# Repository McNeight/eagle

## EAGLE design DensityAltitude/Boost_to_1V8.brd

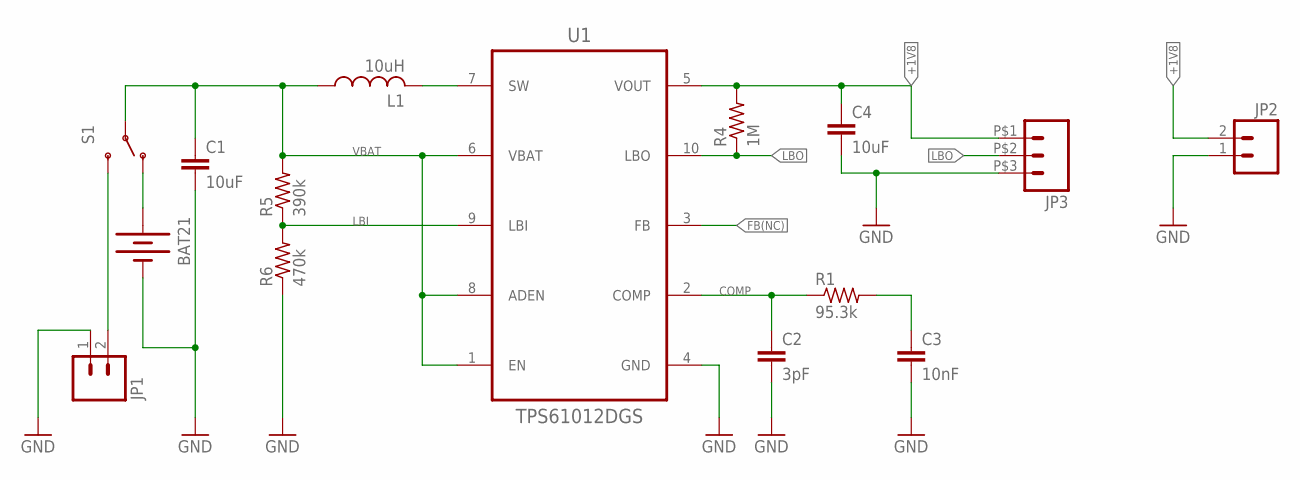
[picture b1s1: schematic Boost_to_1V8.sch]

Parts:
BAT21: BATTERYAA; BATTERY-AA
C1, C4: 10uF; C1812
C2: 3pF; C0805
C3: 10nF; C0805
JP1, JP2: M02JST-PTH-2; JST-2-PTH
JP3: M03; 1X03_282834-3
L1: 10uH; CDRH6D38
R1: 95.3k; R0805
R4: 1M; R0805
R5: 390k; R0805
R6: 470k; R0805
S1: SWITCH-SPDTPTH; SWITCH-SPDT
U1: TPS61012DGS; SOP50P490X110-10N

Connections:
+1V8: C4.1, JP2.2, JP3.P$1 (1), R4.2, U1.5 (VOUT)
BAT+: BAT21.PWR@1 (+), BAT21.PWR@2 (+), S1.1 (O)
COMP: C2.1, R1.1, U1.2 (COMP)
FB(NC): U1.3 (FB)
GND: BAT21.GND@1 (-), BAT21.GND@2 (-), C1.2, C2.2, C3.2, C4.2, JP1.1, JP2.1, JP3.P$3 (3), R6.1, U1.4 (GND)
LBI: R5.1, R6.2, U1.9 (LBI)
LBO: JP3.P$2 (2), R4.1, U1.10 (LBO)
unnamed: C3.1, R1.2
unnamed: JP1.2, S1.3 (S)
SW: L1.P$2 (2), U1.7 (SW)
VBAT: C1.1, L1.P$1 (1), R5.2, S1.2, U1.1 (EN), U1.6 (VBAT), U1.8 (ADEN)

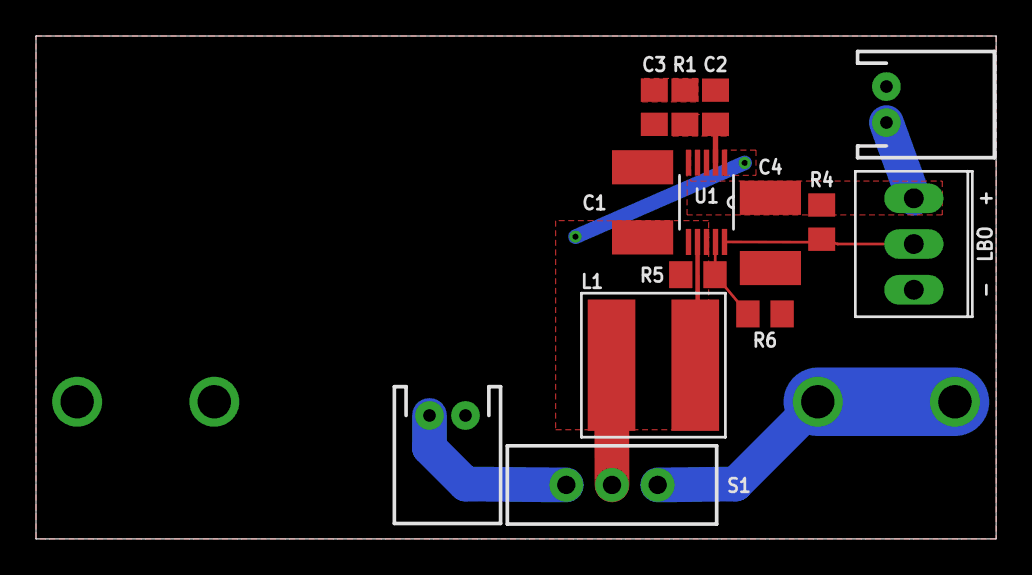
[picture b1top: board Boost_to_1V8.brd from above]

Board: 2 copper layers, 53.3 x 27.9 mm, 15 parts (1 on the bottom side), 10 nets.

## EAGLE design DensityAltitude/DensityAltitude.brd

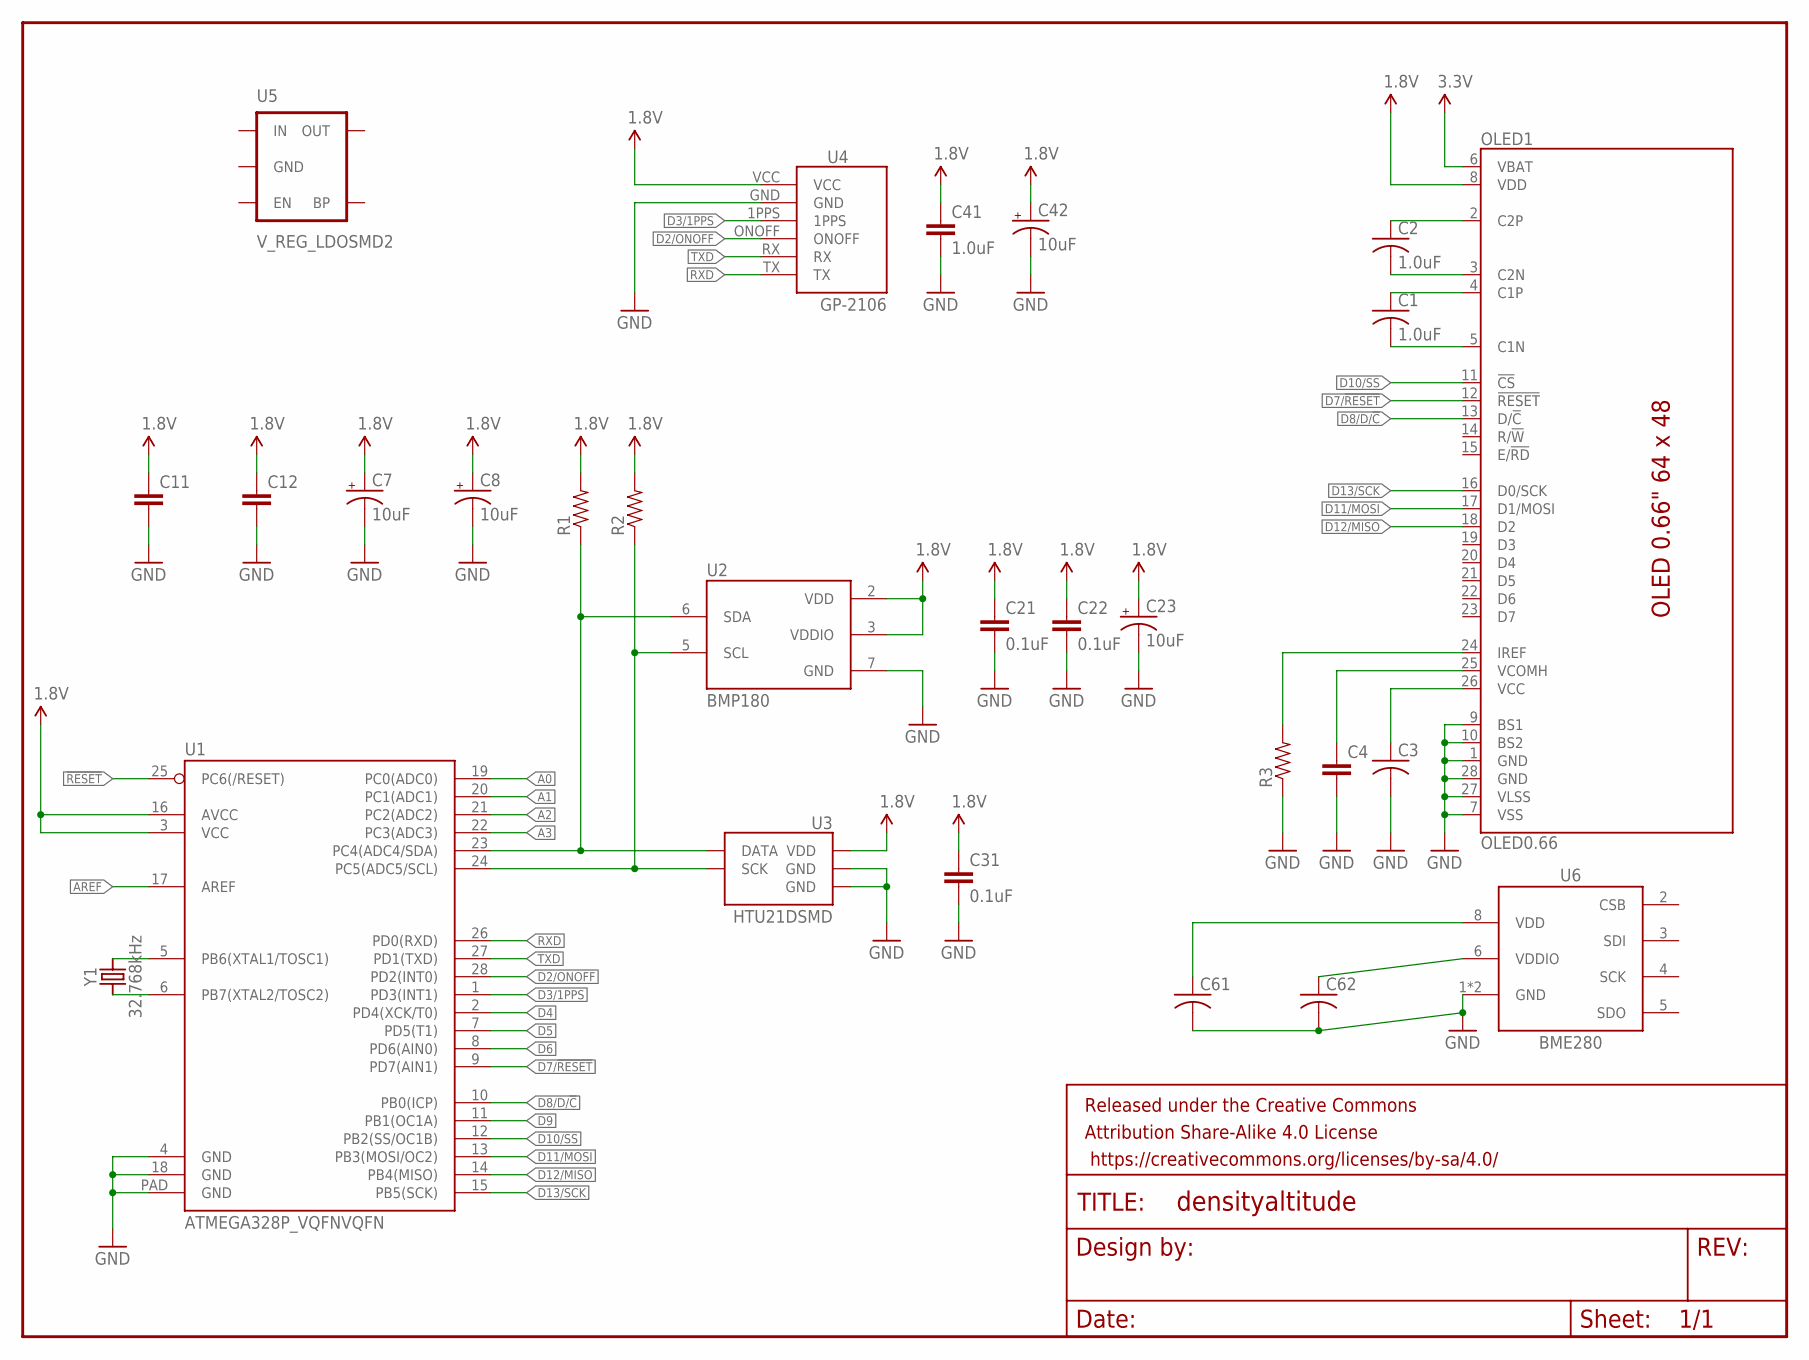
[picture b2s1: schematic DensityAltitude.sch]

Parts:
C1, C2: 1.0uF; C0201
C3, C61, C62: C-USC0201; C0201
C4, C11, C12: CAP0402-CAP; 0402-CAP
C7, C8, C23, C42: 10uF; EIA3216
C21, C22, C31: 0.1uF; 0402-CAP
C41: 1.0uF; 0402-CAP
FRAME1: FRAME-LETTER; CREATIVE_COMMONS
OLED1: OLED0.66; OLED-0.66-64X48
R1, R2, R3: RESISTOR0402-RES; 0402-RES
U1: ATMEGA328P_VQFNVQFN; VQFN-28
U2: BMP180
U3: HTU21DSMD; HTU21D
U4: GP-2106
U5: V_REG_LDOSMD2; SC70
U6: BME280
Y1: 32.768kHz; 2-SMD

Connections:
1.8V: C7.A (+), C8.A (+), C11.1, C12.1, C21.1, C22.1, C23.A (+), C31.1, C41.1, C42.A (+), OLED1.8 (VDD), R1.2, R2.2, U1.3 (VCC), U1.16 (AVCC), U2.2 (VDD), U2.3 (VDDIO), U3.VDD, U4.VCC
3.3V: OLED1.6 (VBAT)
!RESET: U1.25 (PC6(/RESET))
A0: U1.19 (PC0(ADC0))
A1: U1.20 (PC1(ADC1))
A2: U1.21 (PC2(ADC2))
A3: U1.22 (PC3(ADC3))
A4/SDA: R1.1, U1.23 (PC4(ADC4/SDA)), U2.6 (SDA), U3.DATA
A5/SCL: R2.1, U1.24 (PC5(ADC5/SCL)), U2.5 (SCL), U3.SCK
AREF: U1.17 (AREF)
D2/ONOFF: U1.28 (PD2(INT0)), U4.ONOFF
D3/1PPS: U1.1 (PD3(INT1)), U4.1PPS
D4: U1.2 (PD4(XCK/T0))
D5: U1.7 (PD5(T1))
D6: U1.8 (PD6(AIN0))
D7/!RESET: OLED1.12 (!RESET!), U1.9 (PD7(AIN1))
D8/D/!C: OLED1.13 (D/!C!), U1.10 (PB0(ICP))
D9: U1.11 (PB1(OC1A))
D10/SS: OLED1.11 (!CS!), U1.12 (PB2(SS/OC1B))
D11/MOSI: OLED1.17 (D1/MOSI), U1.13 (PB3(MOSI/OC2))
D12/MISO: OLED1.18 (D2), U1.14 (PB4(MISO))
D13/SCK: OLED1.16 (D0/SCK), U1.15 (PB5(SCK))
GND: C3.2, C4.2, C7.C (-), C8.C (-), C11.2, C12.2, C21.2, C22.2, C23.C (-), C31.2, C41.2, C42.C (-), C61.2, C62.2, OLED1.1 (GND), OLED1.7 (VSS), OLED1.9 (BS1), OLED1.10 (BS2), OLED1.27 (VLSS), OLED1.28 (GND), R3.1, U1.4 (GND), U1.18 (GND), U1.PAD (GND), U2.7 (GND), U3.7 (GND), U3.GND, U4.GND, U6.1 (GND), U6.7 (GND)
unnamed: C62.1, U6.6 (VDDIO)
unnamed: C61.1, U6.8 (VDD)
unnamed: U1.5 (PB6(XTAL1/TOSC1)), Y1.2
unnamed: U1.6 (PB7(XTAL2/TOSC2)), Y1.1
unnamed: C2.1, OLED1.2 (C2P)
unnamed: C2.2, OLED1.3 (C2N)
unnamed: C1.1, OLED1.4 (C1P)
unnamed: C1.2, OLED1.5 (C1N)
unnamed: C3.1, OLED1.26 (VCC)
unnamed: C4.1, OLED1.25 (VCOMH)
unnamed: OLED1.24 (IREF), R3.2
RXD: U1.26 (PD0(RXD)), U4.TX
TXD: U1.27 (PD1(TXD)), U4.RX

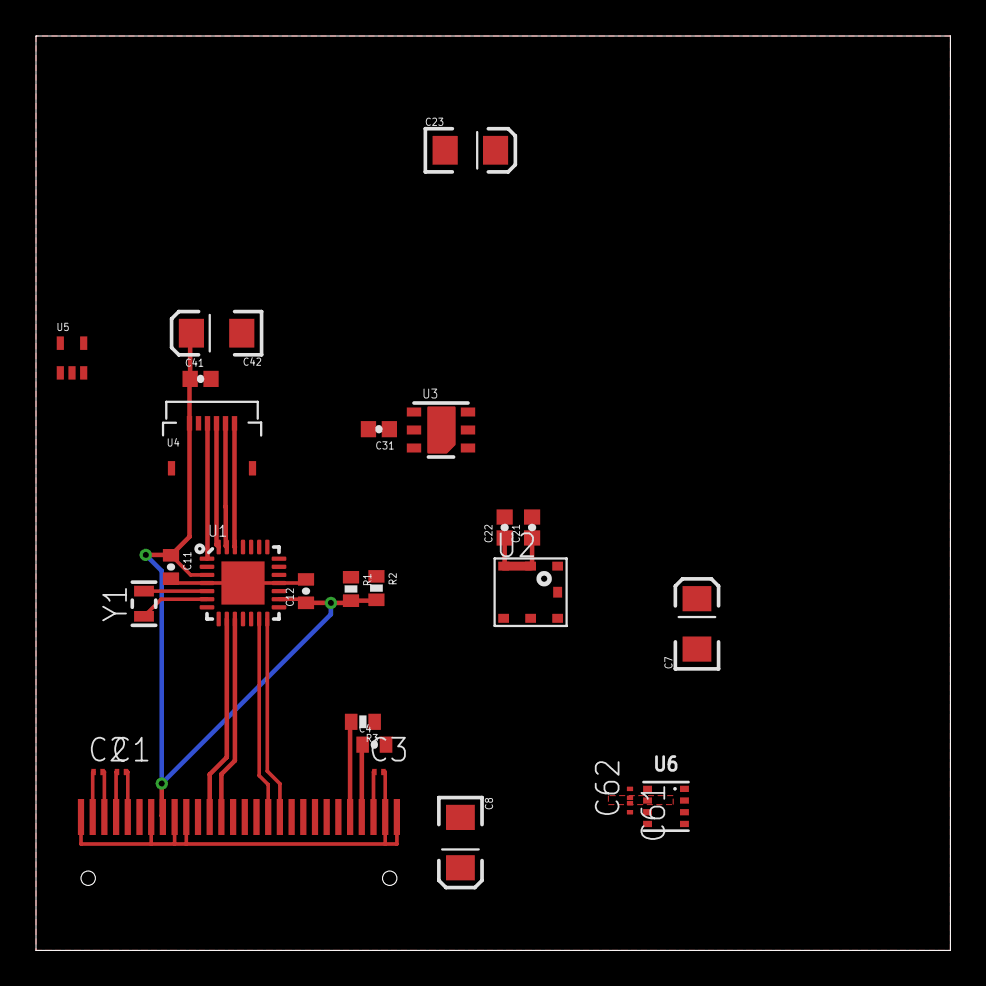
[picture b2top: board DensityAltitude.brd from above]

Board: 2 copper layers, 50.8 x 50.8 mm, 28 parts (0 on the bottom side), 25 nets.

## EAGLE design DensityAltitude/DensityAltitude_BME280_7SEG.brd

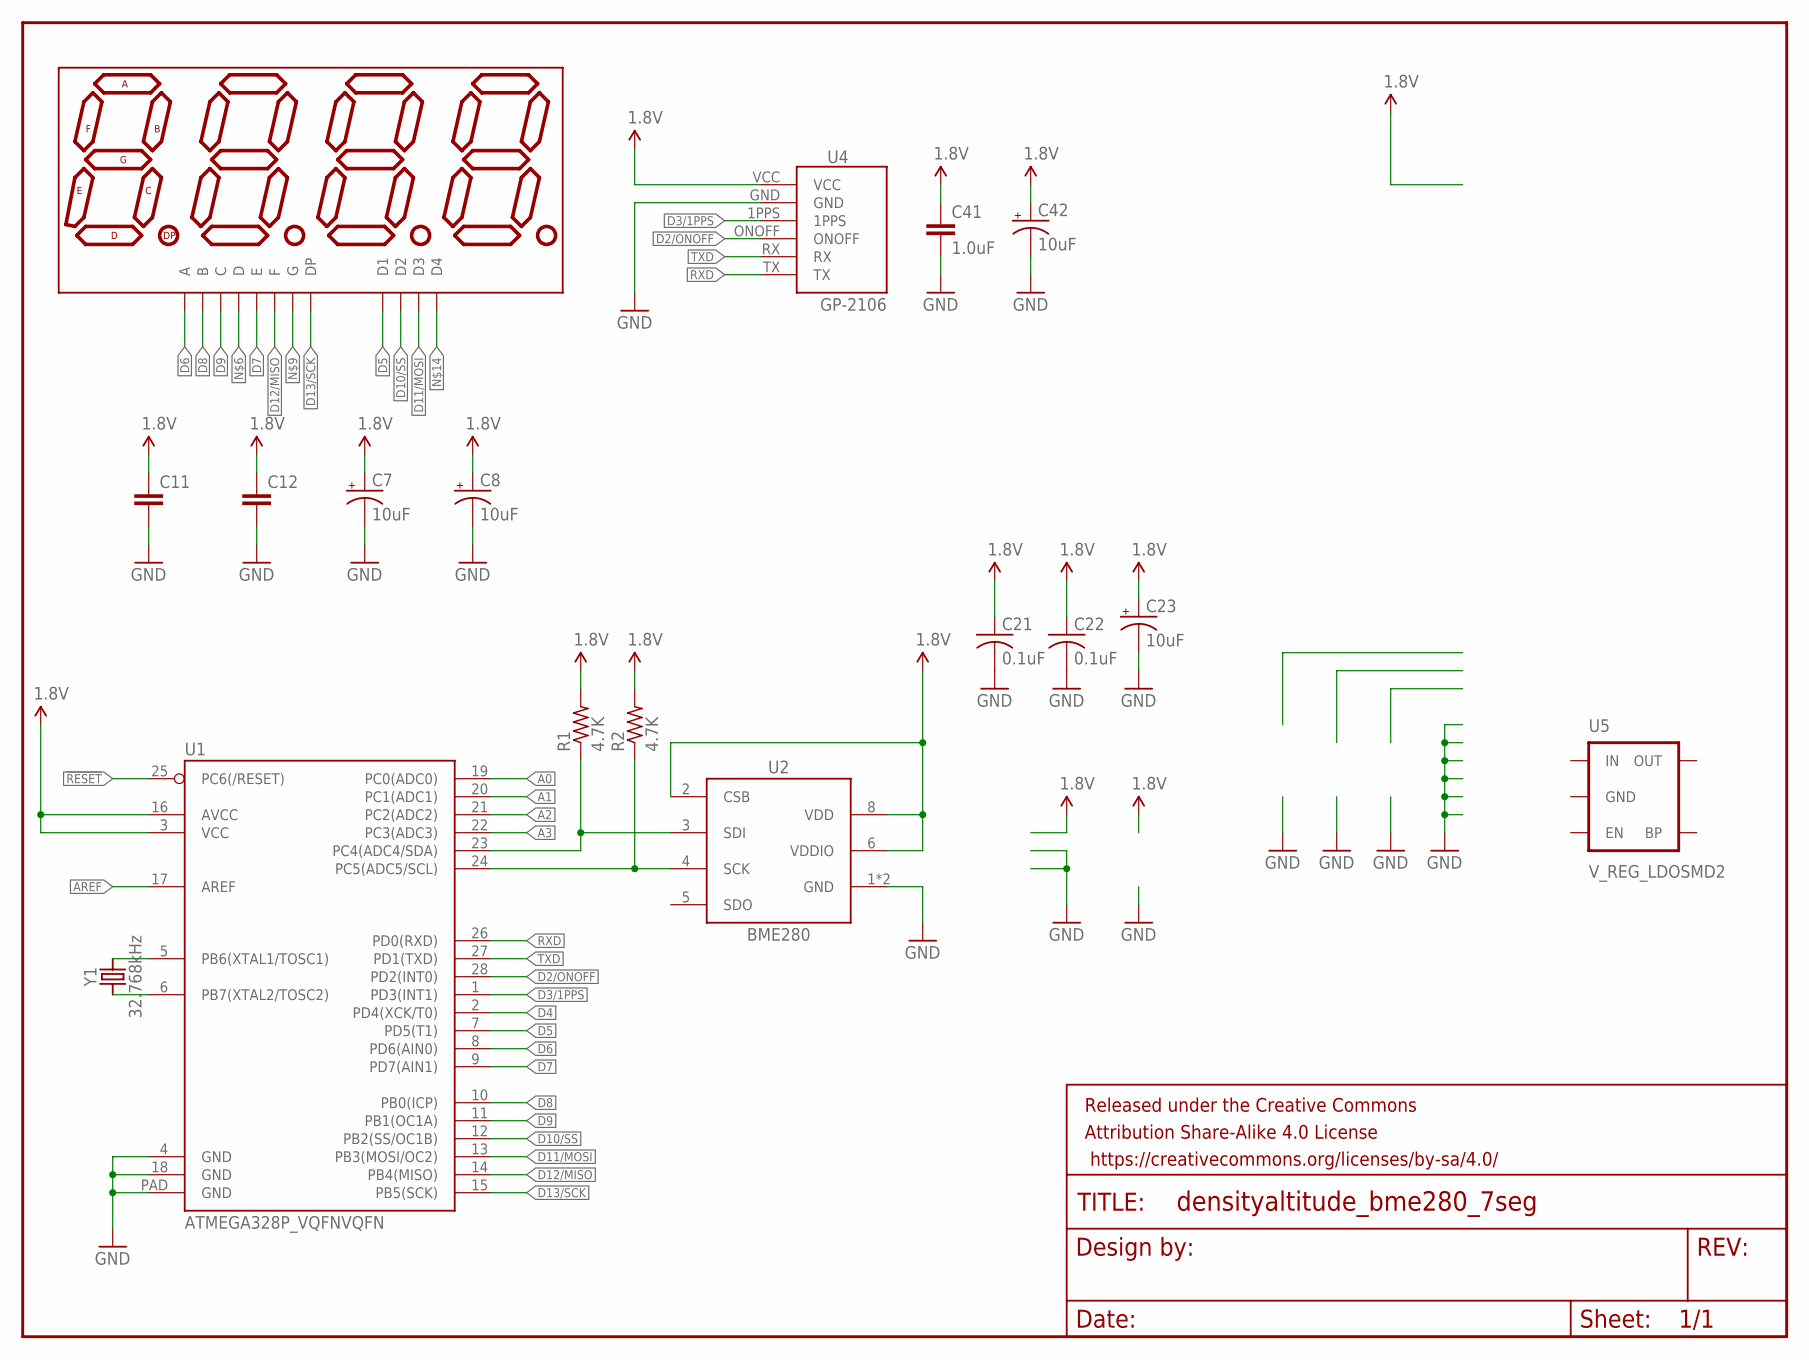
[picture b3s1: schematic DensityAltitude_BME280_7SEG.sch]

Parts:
C7, C8, C23, C42: 10uF; EIA3216
C11, C12: CAP0402-CAP; 0402-CAP
C21, C22: 0.1uF; C0201
C41: 1.0uF; 0402-CAP
DISP1: 7-SEGMENT-4DIGIT-COUNTER-HP-BUBBLE; DIL12
FRAME1: FRAME-LETTER; CREATIVE_COMMONS
R1, R2: 4.7K; R0201
U1: ATMEGA328P_VQFNVQFN; VQFN-28
U2: BME280
U4: GP-2106
U5: V_REG_LDOSMD2; SC70
Y1: 32.768kHz; 2-SMD

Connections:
1.8V: C7.A (+), C8.A (+), C11.1, C12.1, C21.1, C22.1, C23.A (+), C41.1, C42.A (+), R1.2, R2.2, U1.3 (VCC), U1.16 (AVCC), U2.2 (CSB), U2.6 (VDDIO), U2.8 (VDD), U4.VCC
!RESET: U1.25 (PC6(/RESET))
A0: U1.19 (PC0(ADC0))
A1: U1.20 (PC1(ADC1))
A2: U1.21 (PC2(ADC2))
A3: U1.22 (PC3(ADC3))
A4/SDA: R1.1, U1.23 (PC4(ADC4/SDA)), U2.3 (SDI)
A5/SCL: R2.1, U1.24 (PC5(ADC5/SCL)), U2.4 (SCK)
AREF: U1.17 (AREF)
D2/ONOFF: U1.28 (PD2(INT0)), U4.ONOFF
D3/1PPS: U1.1 (PD3(INT1)), U4.1PPS
D4: U1.2 (PD4(XCK/T0))
D5: DISP1.1 (D1), U1.7 (PD5(T1))
D6: DISP1.12 (A), U1.8 (PD6(AIN0))
D7: DISP1.2 (E), U1.9 (PD7(AIN1))
D8: DISP1.11 (B), U1.10 (PB0(ICP))
D9: DISP1.3 (C), U1.11 (PB1(OC1A))
D10/SS: DISP1.10 (D2), U1.12 (PB2(SS/OC1B))
D11/MOSI: DISP1.4 (D3), U1.13 (PB3(MOSI/OC2))
D12/MISO: DISP1.9 (F), U1.14 (PB4(MISO))
D13/SCK: DISP1.5 (DP), U1.15 (PB5(SCK))
GND: C7.C (-), C8.C (-), C11.2, C12.2, C21.2, C22.2, C23.C (-), C41.2, C42.C (-), U1.4 (GND), U1.18 (GND), U1.PAD (GND), U2.1 (GND), U2.7 (GND), U4.GND
unnamed: U1.5 (PB6(XTAL1/TOSC1)), Y1.2
unnamed: U1.6 (PB7(XTAL2/TOSC2)), Y1.1
RXD: U1.26 (PD0(RXD)), U4.TX
TXD: U1.27 (PD1(TXD)), U4.RX

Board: 2 copper layers, 18 parts (0 on the bottom side), 19 nets, no tracks yet.

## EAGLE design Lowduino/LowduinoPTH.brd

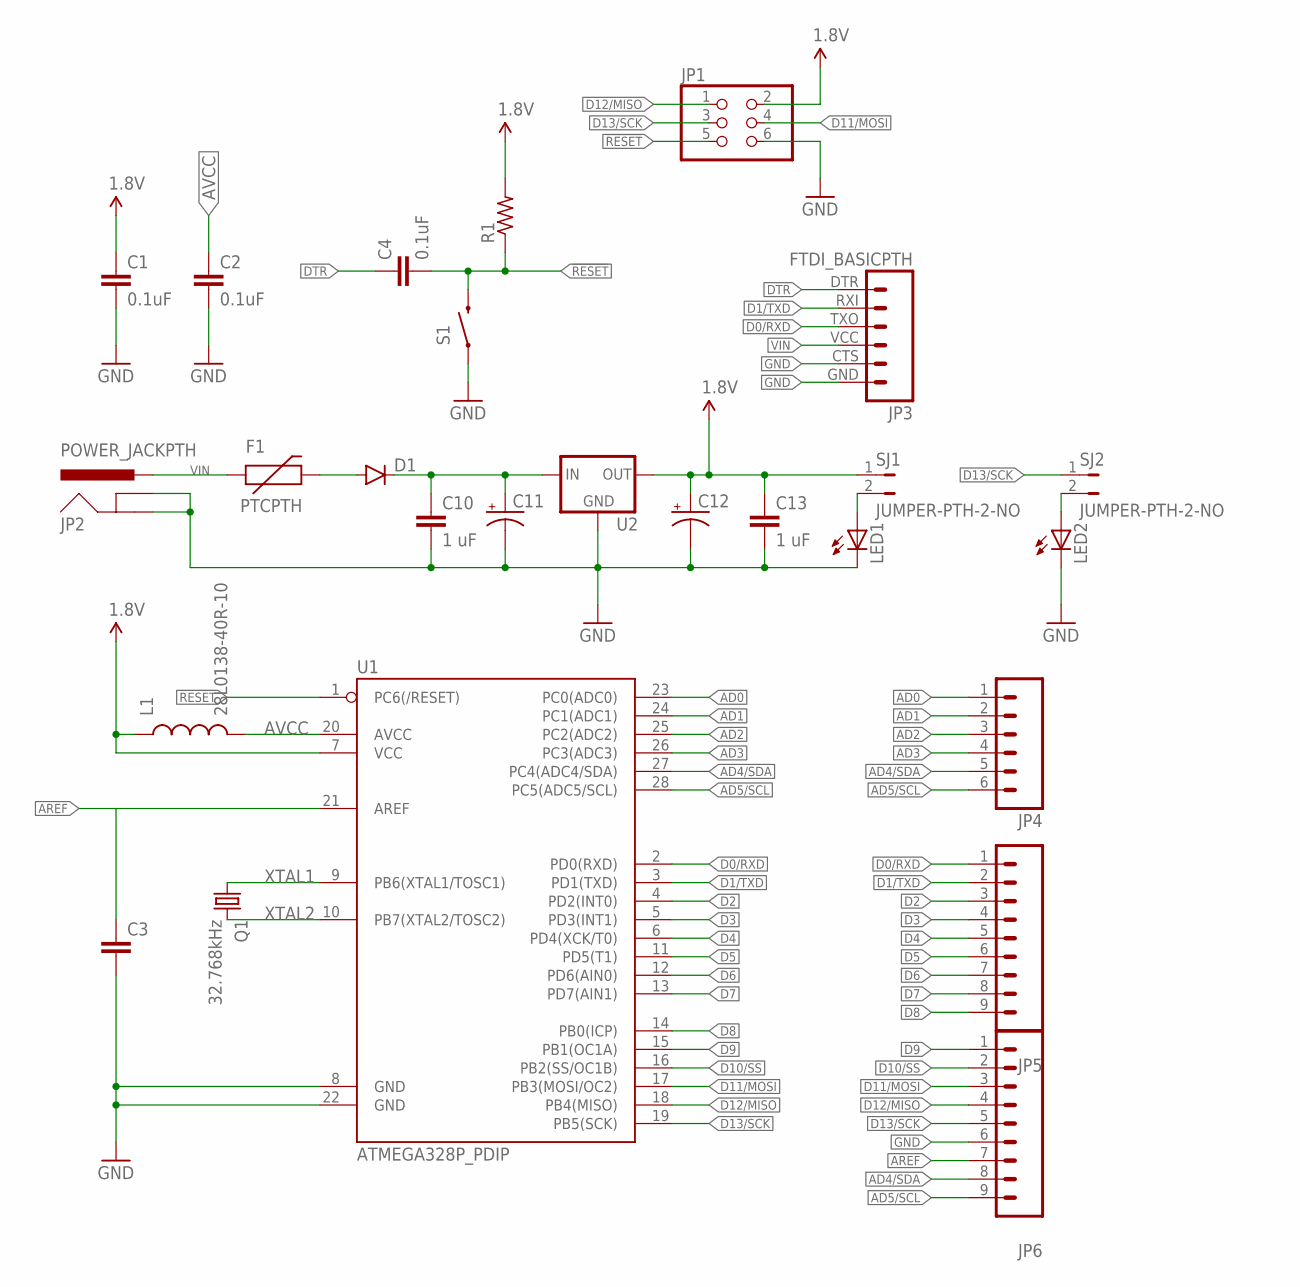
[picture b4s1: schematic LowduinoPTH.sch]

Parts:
C1: 0.1uF; CAP-PTH-SMALL2
C2: 0.1uF; CAP-PTH-5MM
C3: CAPPTH2; CAP-PTH-SMALL2
C4: 0.1uF; CAP-PTH-LARGE
C10, C13: 1 uF; CAP-PTH-SMALL2
C11, C12: CPOL-USE2.5-6; E2,5-6
D1: DIODEPTH; DIODE-1N4001
F1: PTCPTH; PTC
JP1: PINHD-2X3; 2X03
JP2: POWER_JACKPTH; POWER_JACK_PTH
JP3: FTDI_BASICPTH; FTDI_BASIC
JP4: M06SILK_FEMALE_PTH; 1X06
JP5, JP6: M09; 1X09
L1: 28L0138-40R-10; AXIAL-0.6
LED1, LED2: LED3MM
Q1: 32.768kHz; TC26H
R1: R-US_0207/10; 0207/10
S1: SWITCH-MOMENTARY-2PTH; TACTILE-PTH
SJ1, SJ2: JUMPER-PTH-2-NO; PTH-JUMPER-2-NO_NO_SILK
U1: ATMEGA328P_PDIP; DIL28-3
U2: V_REG_78XXTO-92_UNTESTED; TO-92

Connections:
1.8V: C1.1, C12.+, C13.1, JP1.2, L1.P$1 (1), R1.2, SJ1.1, U1.7 (VCC), U2.3 (OUT)
!RESET: C4.2, JP1.5, R1.1, S1.3 (2), U1.1 (PC6(/RESET))
AD0: JP4.1, U1.23 (PC0(ADC0))
AD1: JP4.2, U1.24 (PC1(ADC1))
AD2: JP4.3, U1.25 (PC2(ADC2))
AD3: JP4.4, U1.26 (PC3(ADC3))
AD4/SDA: JP4.5, JP6.8, U1.27 (PC4(ADC4/SDA))
AD5/SCL: JP4.6, JP6.9, U1.28 (PC5(ADC5/SCL))
AREF: C3.1, JP6.7, U1.21 (AREF)
AVCC: C2.1, L1.P$2 (2), U1.20 (AVCC)
D0/RXD: JP3.TXO (3), JP5.1, U1.2 (PD0(RXD))
D1/TXD: JP3.RXI (2), JP5.2, U1.3 (PD1(TXD))
D2: JP5.3, U1.4 (PD2(INT0))
D3: JP5.4, U1.5 (PD3(INT1))
D4: JP5.5, U1.6 (PD4(XCK/T0))
D5: JP5.6, U1.11 (PD5(T1))
D6: JP5.7, U1.12 (PD6(AIN0))
D7: JP5.8, U1.13 (PD7(AIN1))
D8: JP5.9, U1.14 (PB0(ICP))
D9: JP6.1, U1.15 (PB1(OC1A))
D10/SS: JP6.2, U1.16 (PB2(SS/OC1B))
D11/MOSI: JP1.4, JP6.3, U1.17 (PB3(MOSI/OC2))
D12/MISO: JP1.1, JP6.4, U1.18 (PB4(MISO))
D13/SCK: JP1.3, JP6.5, SJ2.1, U1.19 (PB5(SCK))
DTR: C4.1, JP3.DTR (1)
GND: C1.2, C2.2, C3.2, C10.2, C11.-, C12.-, C13.2, JP1.6, JP2.GND, JP2.GNDBREAK, JP3.CTS (5), JP3.GND (6), JP6.6, LED1.K (C), LED2.K (C), S1.1, U1.8 (GND), U1.22 (GND), U2.1 (GND)
unnamed: LED1.A, SJ1.2
unnamed: LED2.A, SJ2.2
unnamed: D1.A, F1.P$2 (2)
unnamed: C10.1, C11.+, D1.C, U2.2 (IN)
VIN: F1.P$1 (1), JP2.PWR, JP3.VCC (4)
XTAL1: Q1.1, U1.9 (PB6(XTAL1/TOSC1))
XTAL2: Q1.2, U1.10 (PB7(XTAL2/TOSC2))

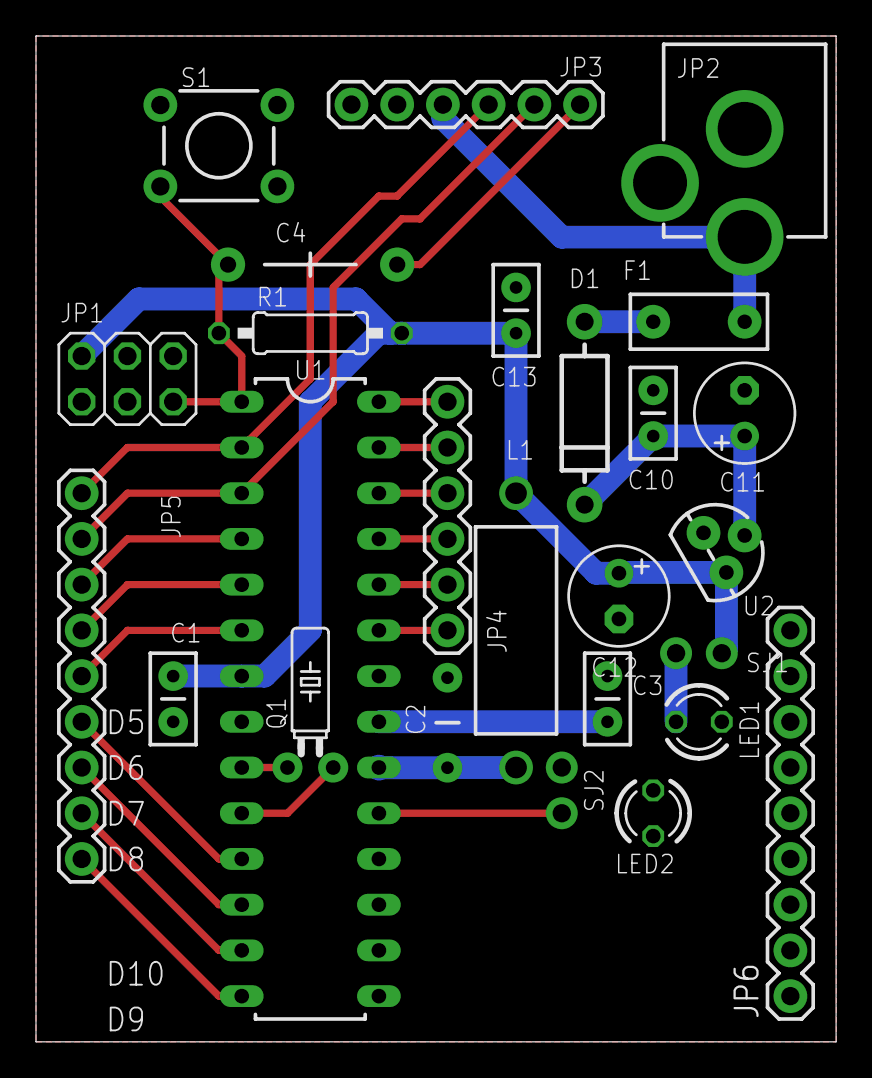
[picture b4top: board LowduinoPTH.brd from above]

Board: 2 copper layers, 44.5 x 55.9 mm, 26 parts (0 on the bottom side), 33 nets.

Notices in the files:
parts and their libraries:
SparkFun-Electromechanical: Licensing: Creative Commons ShareAlike 4.0 International - https://creativecommons.org/licenses/by-sa/4.0
SparkFun-Aesthetics: Released under the Creative Commons Attribution Share-Alike 4.0 License
SparkFun-Aesthetics: https://creativecommons.org/licenses/by-sa/4.0
